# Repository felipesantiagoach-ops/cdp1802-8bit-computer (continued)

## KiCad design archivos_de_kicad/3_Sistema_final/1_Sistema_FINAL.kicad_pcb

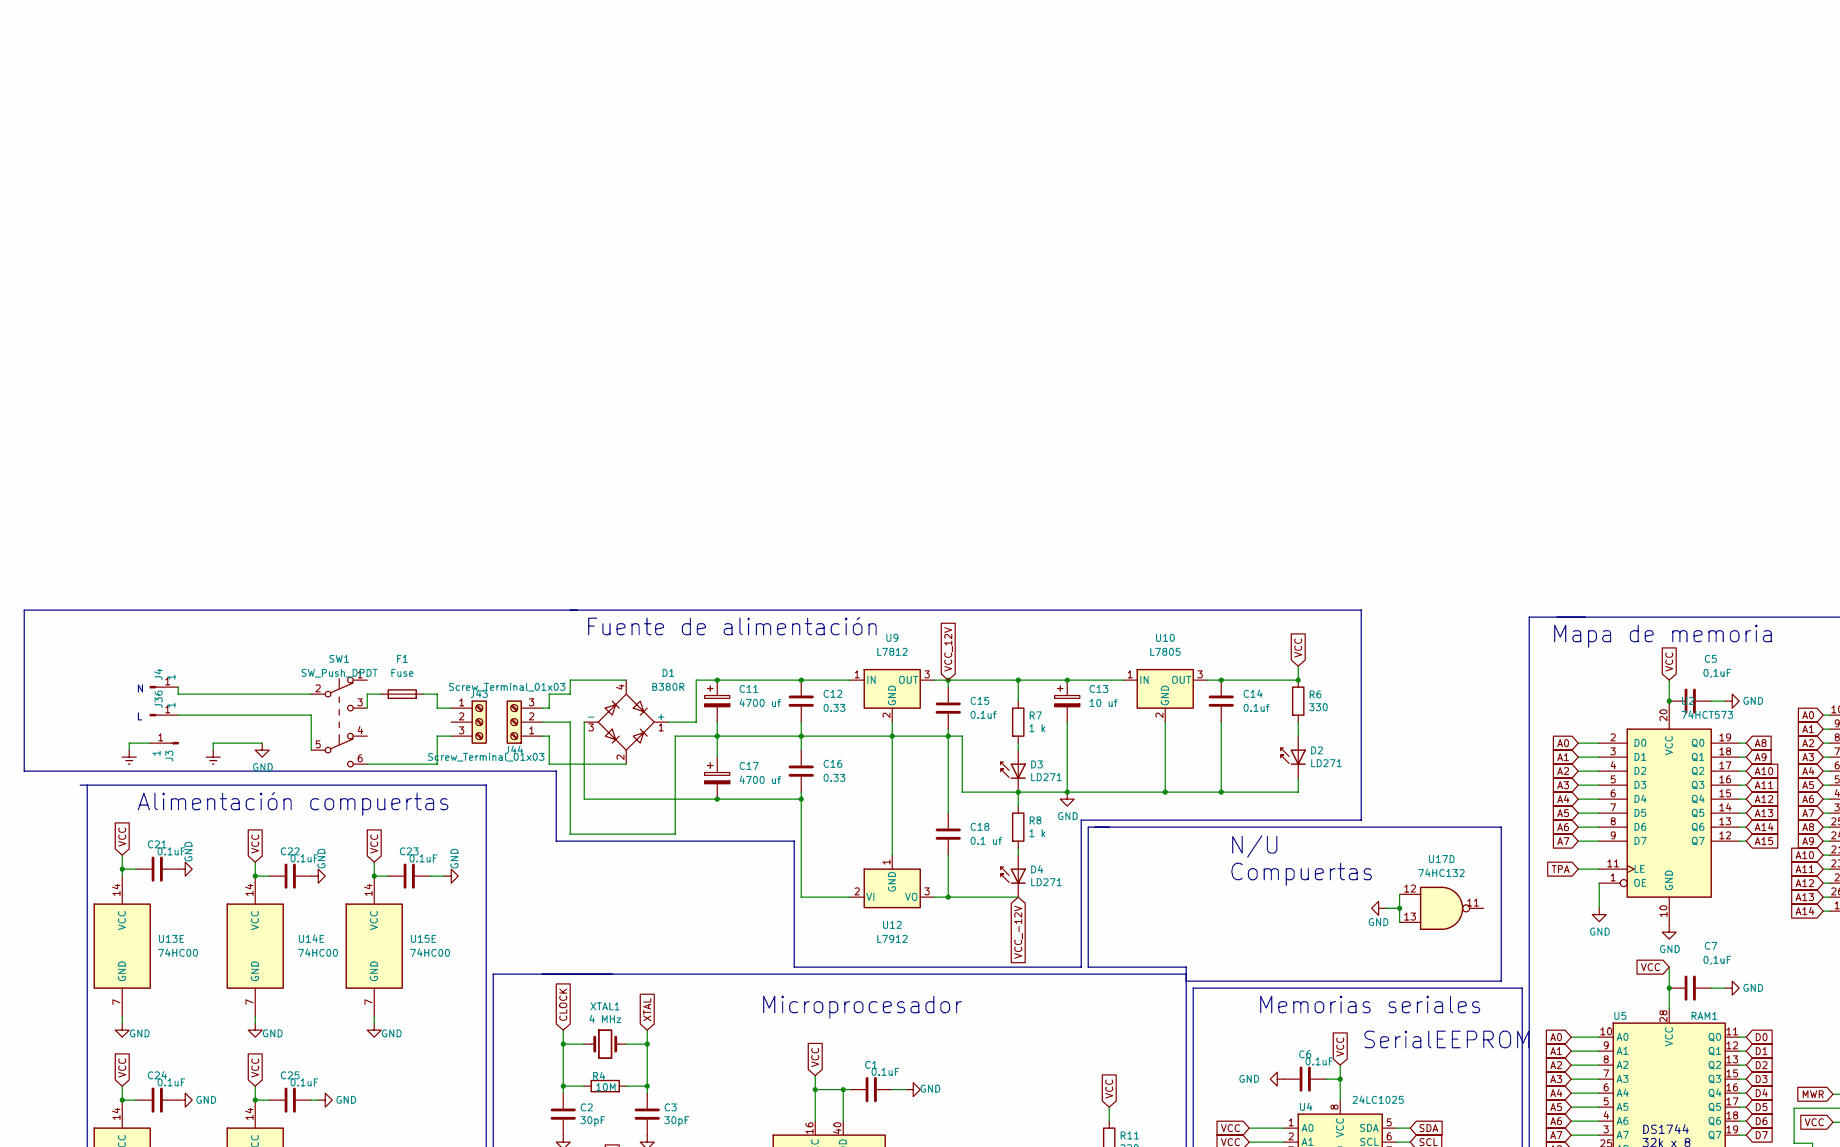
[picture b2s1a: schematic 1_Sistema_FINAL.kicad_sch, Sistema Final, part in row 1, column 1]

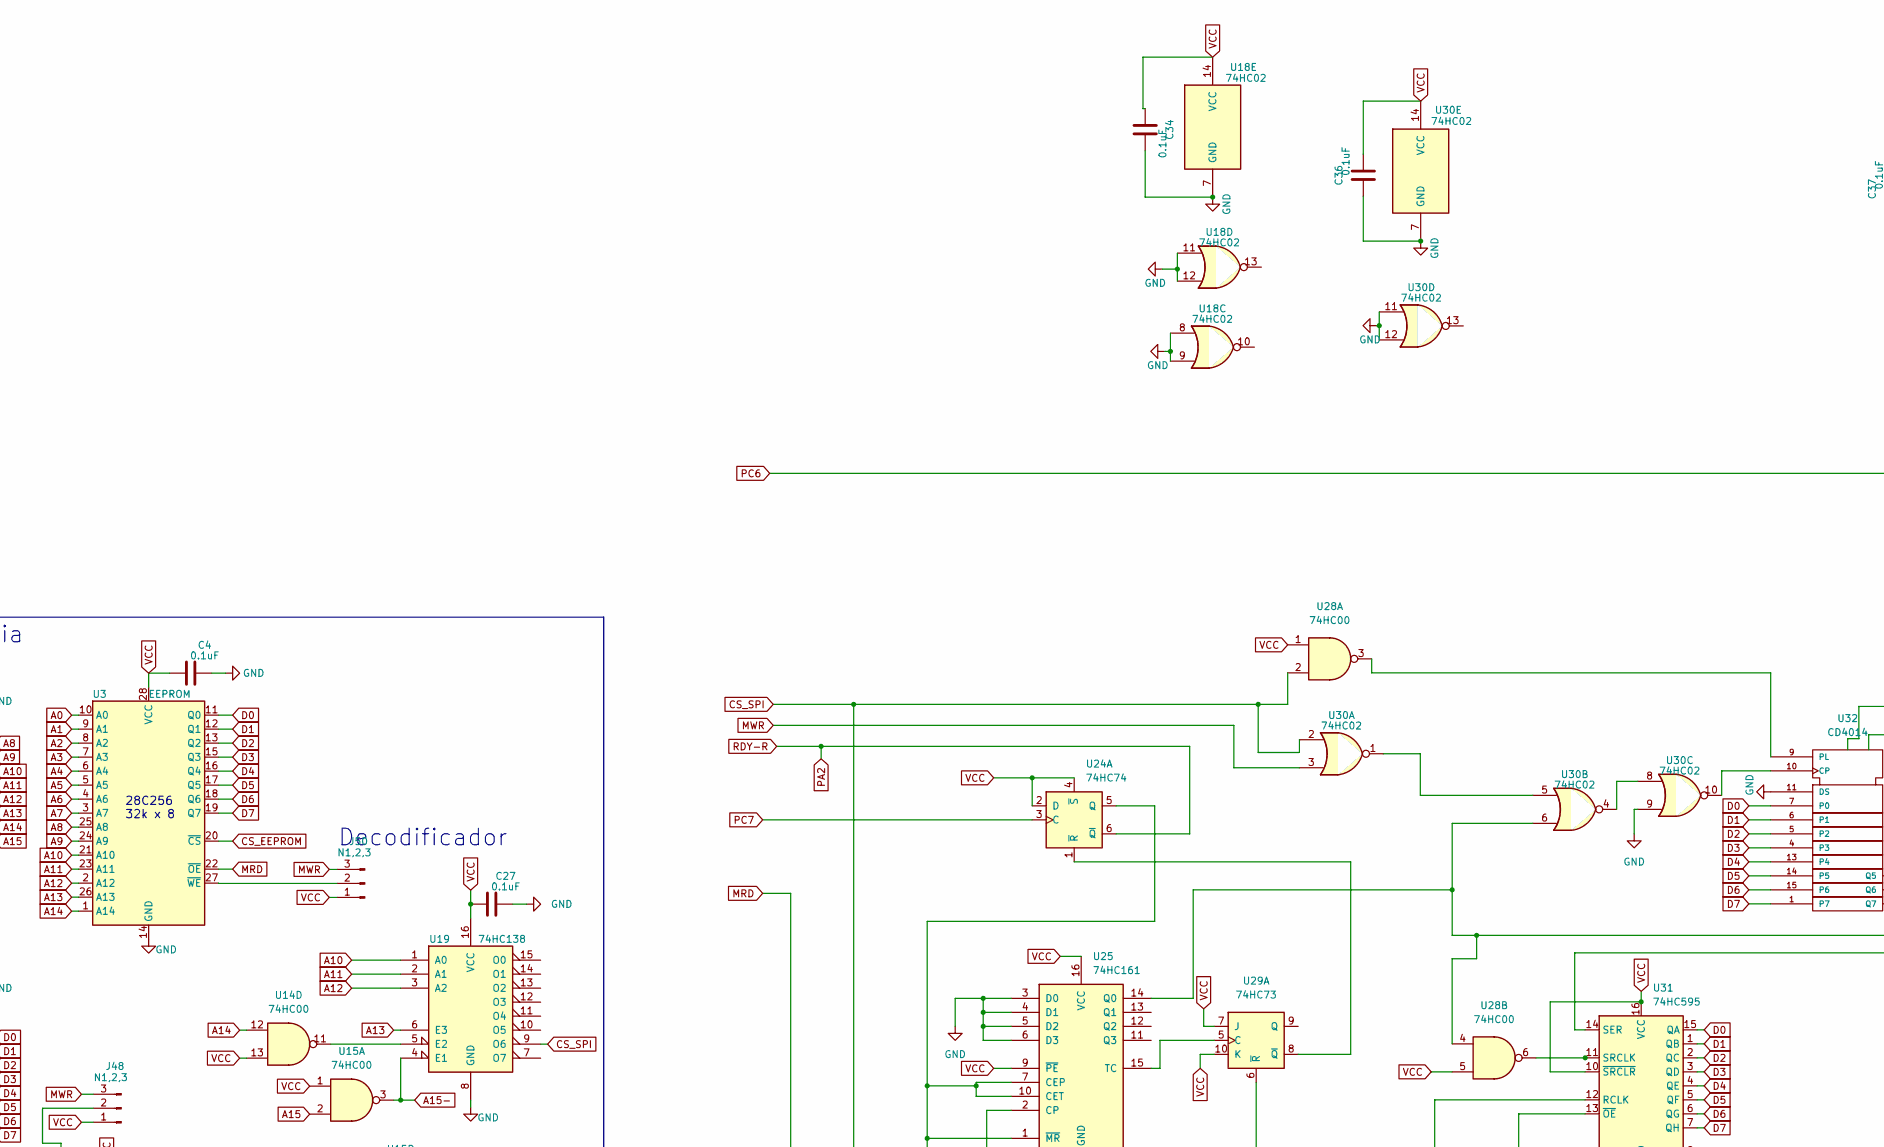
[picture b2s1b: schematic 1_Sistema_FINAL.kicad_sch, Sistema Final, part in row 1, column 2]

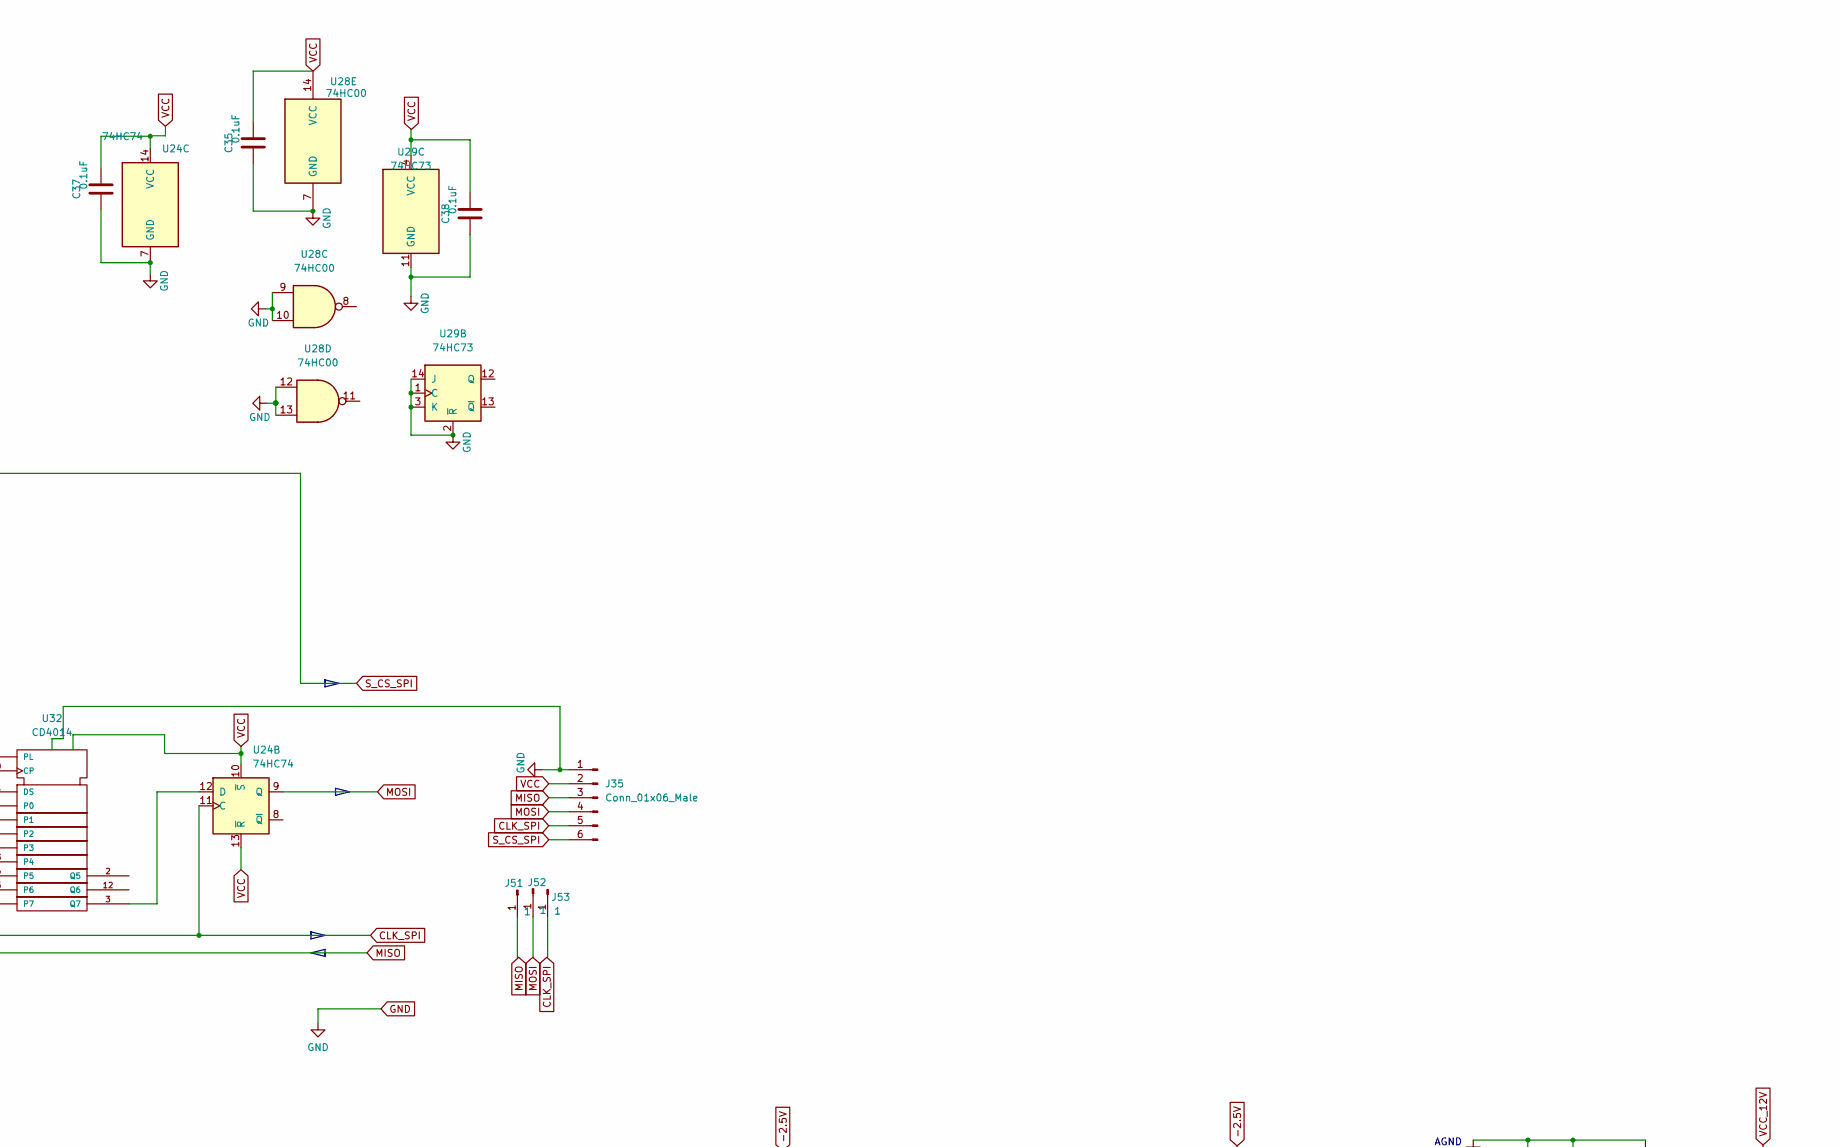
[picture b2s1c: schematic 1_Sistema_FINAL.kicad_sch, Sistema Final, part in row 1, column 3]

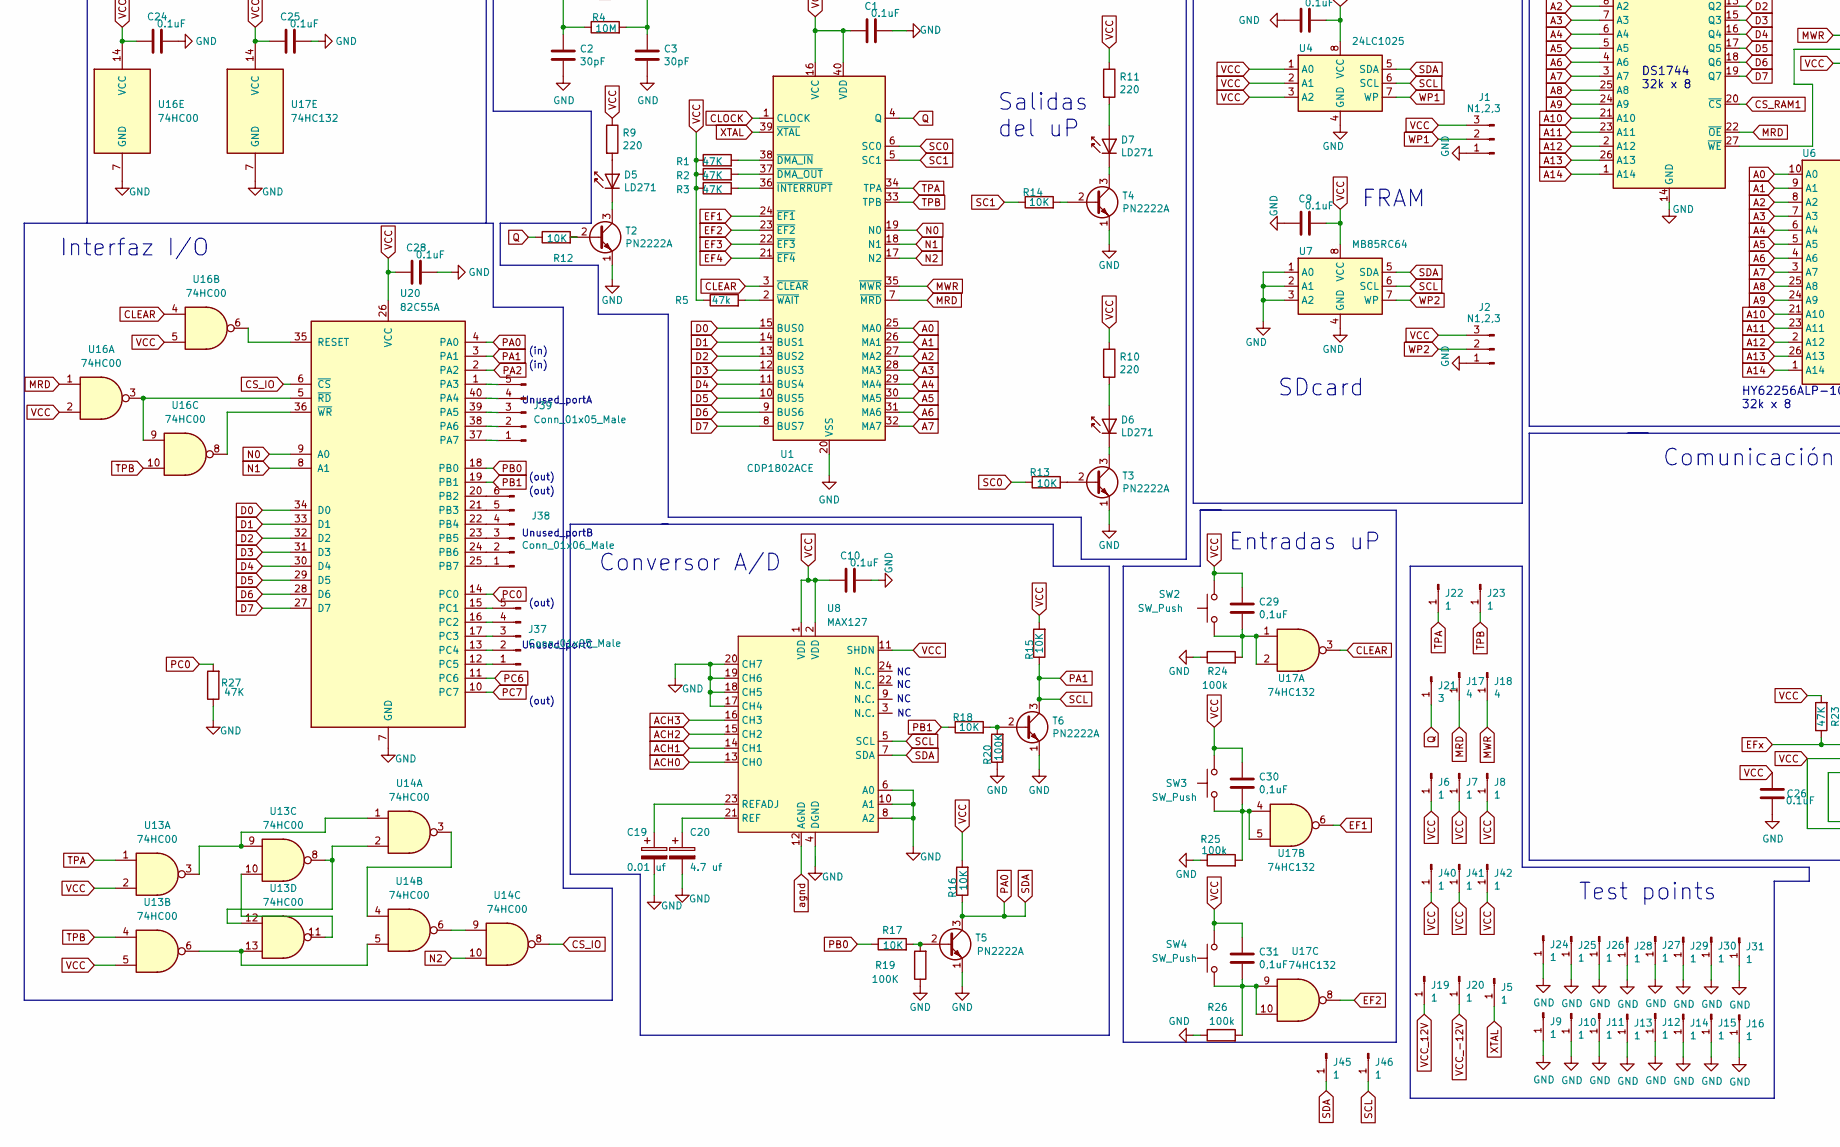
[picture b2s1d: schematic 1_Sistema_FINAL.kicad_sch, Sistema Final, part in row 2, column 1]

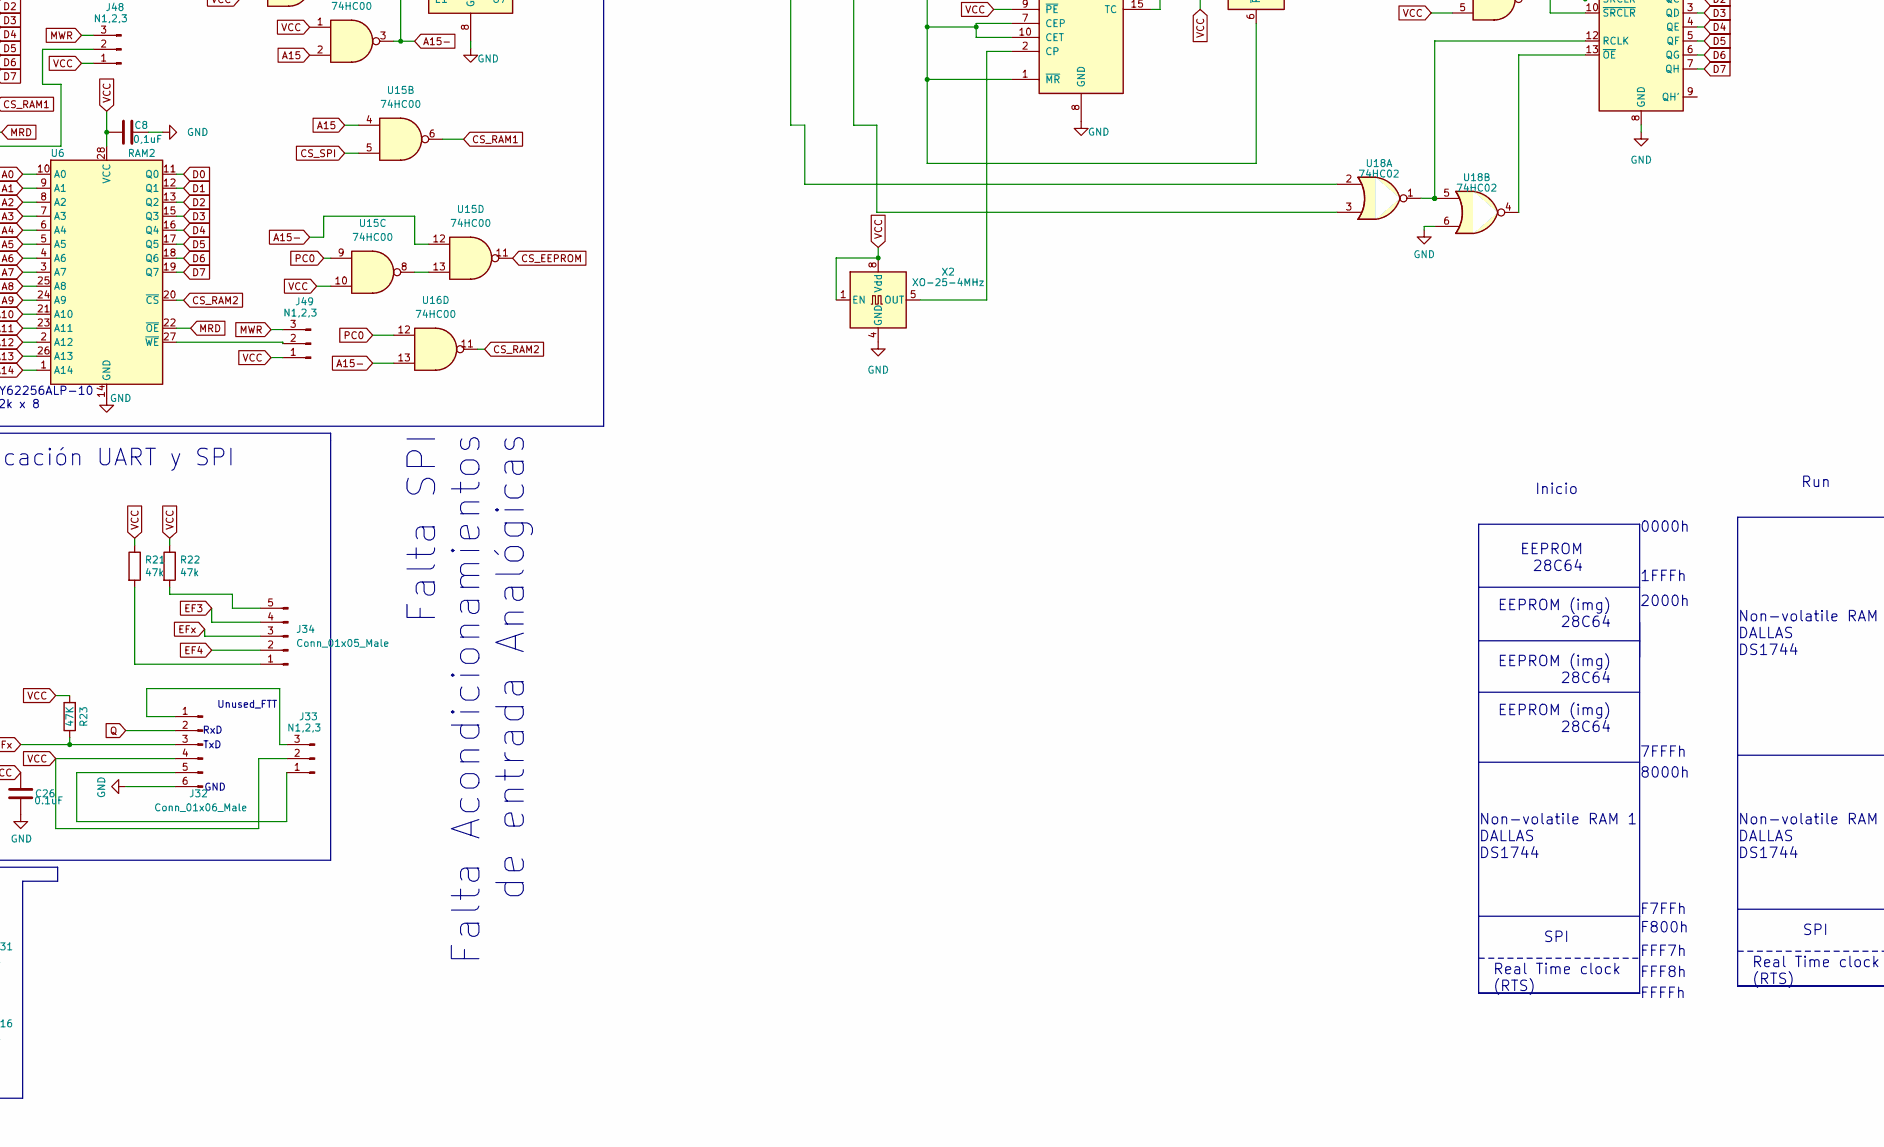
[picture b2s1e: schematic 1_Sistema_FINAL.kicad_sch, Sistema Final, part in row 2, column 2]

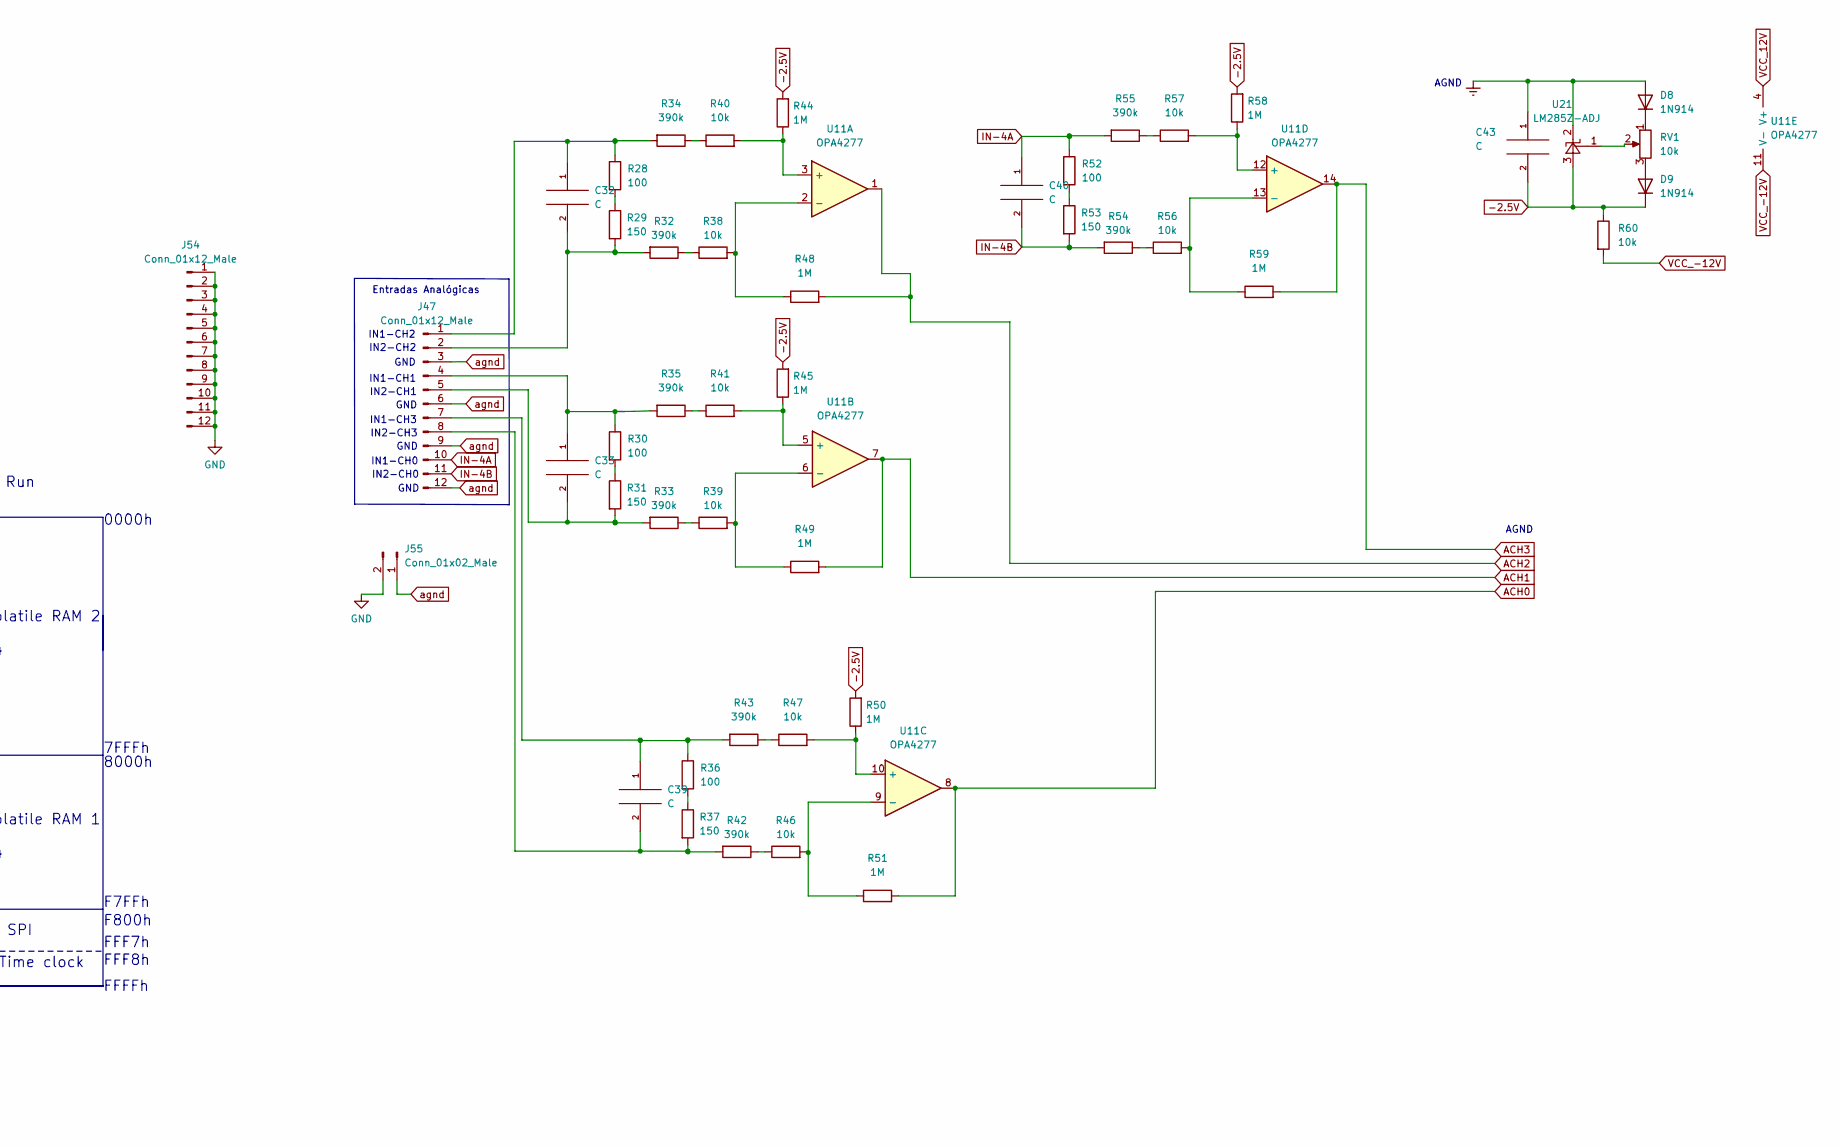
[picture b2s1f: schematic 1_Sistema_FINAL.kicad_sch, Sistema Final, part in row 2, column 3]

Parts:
C1, C4, C6, C9, C10, C21, C22, C23, C24, C25, C26, C27, C28, C34, C35, C36, C37, C38: 0.1uF; C_Disc_D3.0mm_W1.6mm_P2.50mm
C2, C3: 30pF; C_Disc_D4.3mm_W1.9mm_P5.00mm
C5, C7, C8, C29, C30, C31: 0,1uF; C_Disc_D3.0mm_W1.6mm_P2.50mm
C11: 4700 uf; C_Rect_L11.5mm_W4.3mm_P10.00mm_MKT
C12, C16: 0.33; C_Disc_D3.0mm_W1.6mm_P2.50mm
C13: 10 uf; CP_Radial_D5.0mm_P2.00mm
C14, C15: 0.1uf; C_Disc_D3.0mm_W1.6mm_P2.50mm
C17: 4700 uf; C_Rect_L11.5mm_W2.8mm_P10.00mm_MKT
C18: 0.1 uf; C_Disc_D3.0mm_W1.6mm_P2.50mm
C19: 0.01 uf; C_Disc_D3.0mm_W1.6mm_P2.50mm
C20: 4.7 uf; CP_Radial_D5.0mm_P2.00mm
C32, C33, C39, C40, C43: C; C_Disc_D3.0mm_W1.6mm_P2.50mm
D1: B380R; Diode_Bridge_Round_D9.0mm
D2, D3, D4, D5, D6, D7: LD271; LED_D5.0mm
D8, D9: 1N914; D_DO-35_SOD27_P7.62mm_Horizontal
F1: Fuse; fusible_10mm
J1, J2, J33, J48, J49, J50: N1,2,3; PinHeader_1x03_P2.54mm_Vertical
J3, J4, J5, J6, J7, J8, J9, J10, J11, J12, J13, J14, J15, J16, J19, J20, J22, J23, J24, J25, J26, J27, J28, J29, J30, J31, J36, J40, J41, J42, J45, J46, J51, J52, J53: 1; Pin_D1.0mm_L10.0mm
J17, J18: 4; Pin_D1.0mm_L10.0mm
J21: 3; Pin_D1.0mm_L10.0mm
J32, J35, J38: Conn_01x06_Male; PinHeader_1x06_P2.54mm_Vertical
J34, J37, J39: Conn_01x05_Male; PinHeader_1x05_P2.54mm_Vertical
J43, J44: Screw_Terminal_01x03; TerminalBlock_bornier-3_P5.08mm
J47, J54: Conn_01x12_Male; PinHeader_1x12_P2.54mm_Vertical
J55: Conn_01x02_Male; PinHeader_1x02_P2.54mm_Vertical
R1, R2, R3, R23, R27: 47K; R_Axial_DIN0207_L6.3mm_D2.5mm_P10.16mm_Horizontal
R4: 10M; R_Axial_DIN0207_L6.3mm_D2.5mm_P10.16mm_Horizontal
R5: 47k; R_Axial_DIN0207_L6.3mm_D2.5mm_P10.16mm_Horizontal
R6: 330; R_Axial_DIN0207_L6.3mm_D2.5mm_P10.16mm_Horizontal
R7, R8: 1 k; R_Axial_DIN0207_L6.3mm_D2.5mm_P10.16mm_Horizontal
R9, R10, R11: 220; R_Axial_DIN0207_L6.3mm_D2.5mm_P10.16mm_Horizontal
R12, R13, R14, R15, R16, R17, R18: 10K; R_Axial_DIN0207_L6.3mm_D2.5mm_P10.16mm_Horizontal
R19, R20: 100K; R_Axial_DIN0207_L6.3mm_D2.5mm_P10.16mm_Horizontal
R21, R22: 47k; R_Axial_DIN0207_L6.3mm_D2.5mm_P15.24mm_Horizontal
R24, R25, R26: 100k; R_Axial_DIN0207_L6.3mm_D2.5mm_P10.16mm_Horizontal
R28, R30, R36, R52: 100; R_Axial_DIN0207_L6.3mm_D2.5mm_P10.16mm_Horizontal
R29, R31, R37, R53: 150; R_Axial_DIN0207_L6.3mm_D2.5mm_P10.16mm_Horizontal
R32, R33, R34, R35, R42, R43, R54, R55: 390k; R_Axial_DIN0207_L6.3mm_D2.5mm_P10.16mm_Horizontal
R38, R39, R40, R41, R46, R47, R56, R57, R60: 10k; R_Axial_DIN0207_L6.3mm_D2.5mm_P10.16mm_Horizontal
R44, R45, R48, R49, R50, R51, R58, R59: 1M; R_Axial_DIN0207_L6.3mm_D2.5mm_P10.16mm_Horizontal
RV1: 10k; Potentiometer_Bourns_3386C_Horizontal
SW1: SW_Push_DPDT; llave_6pin
SW2, SW3, SW4: SW_Push; SW_PUSH_6mm_H4.3mm
T2, T3, T4, T5, T6: PN2222A; TO-92L_Wide
U1: CDP1802ACE; DIP-40_W15.24mm_LongPads
U2: 74HCT573; DIP-20_W7.62mm_Socket_LongPads
U3: EEPROM; DIP-28_W15.24mm_LongPads
U4: 24LC1025; DIP-8_W7.62mm_LongPads
U5: RAM1; DIP-28_W15.24mm_LongPads
U6: RAM2; DIP-28_W15.24mm_LongPads
U7: MB85RC64; DIP-8_W8.89mm_SMDSocket_LongPads
U8: MAX127; DIP-24_W7.62mm_LongPads
U9: L7812; TO-220-3_Vertical
U10: L7805; TO-220-3_Vertical
U11: OPA4277; DIP-14_W7.62mm_LongPads
U12: L7912; TO-220-3_Vertical
U13, U14, U15, U16, U28: 74HC00; DIP-14_W7.62mm_LongPads
U17: 74HC132; DIP-14_W7.62mm_LongPads
U18, U30: 74HC02; DIP-14_W7.62mm_LongPads
U19: 74HC138; DIP-16_W7.62mm_LongPads
U20: 82C55A; DIP-40_W15.24mm
U21: LM285Z-ADJ; TO-92S_Wide
U24: 74HC74; DIP-14_W7.62mm_LongPads
U25: 74HC161; DIP-16_W7.62mm_LongPads
U29: 74HC73; DIP-14_W7.62mm_LongPads
U31: 74HC595; DIP-16_W7.62mm_LongPads
U32: CD4014; DIP-16_W7.62mm_LongPads
X2: XO-25-4MHz; Oscillator_SeikoEpson_SG-8002DC
XTAL1: 4 MHz; Crystal_HC18-U_Vertical

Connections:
-2.5V: C43.2, D9.1 (K), R44.2, R45.2, R50.2, R58.2, R60.1, U21.3 (A)
A0: U1.25 (MA0), U2.2 (D0), U3.10 (A0), U5.10 (A0), U6.10 (A0)
A1: U1.26 (MA1), U2.3 (D1), U3.9 (A1), U5.9 (A1), U6.9 (A1)
A2: U1.27 (MA2), U2.4 (D2), U3.8 (A2), U5.8 (A2), U6.8 (A2)
A3: U1.28 (MA3), U2.5 (D3), U3.7 (A3), U5.7 (A3), U6.7 (A3)
A4: U1.29 (MA4), U2.6 (D4), U3.6 (A4), U5.6 (A4), U6.6 (A4)
A5: U1.30 (MA5), U2.7 (D5), U3.5 (A5), U5.5 (A5), U6.5 (A5)
A6: U1.31 (MA6), U2.8 (D6), U3.4 (A6), U5.4 (A6), U6.4 (A6)
A7: U1.32 (MA7), U2.9 (D7), U3.3 (A7), U5.3 (A7), U6.3 (A7)
A8: U2.19 (Q0), U3.25 (A8), U5.25 (A8), U6.25 (A8)
A9: U2.18 (Q1), U3.24 (A9), U5.24 (A9), U6.24 (A9)
A10: U2.17 (Q2), U3.21 (A10), U5.21 (A10), U6.21 (A10), U19.1 (A0)
A11: U2.16 (Q3), U3.23 (A11), U5.23 (A11), U6.23 (A11), U19.2 (A1)
A12: U2.15 (Q4), U3.2 (A12), U5.2 (A12), U6.2 (A12), U19.3 (A2)
A13: U2.14 (Q5), U3.26 (A13), U5.26 (A13), U6.26 (A13), U19.6 (E3)
A14: U2.13 (Q6), U3.1 (A14), U5.1 (A14), U6.1 (A14), U14.12
A15: U2.12 (Q7), U15.2, U15.4
A15-: U15.3, U15.12, U16.13, U19.4 (E1)
ACH0: R51.2, U8.13 (CH0), U11.8
ACH1: R49.2, U8.14 (CH1), U11.7
ACH2: R48.2, U8.15 (CH2), U11.1
ACH3: R59.2, U8.16 (CH3), U11.14
CLEAR: U1.3 (~CLEAR), U16.4, U17.3
CLK_SPI: J35.5, J53.1, U24.11 (C), U25.14 (Q0), U28.4, U30.6
CLOCK: C2.1, R4.1, U1.1 (CLOCK), XTAL1.1
CS_EEPROM: U3.20 (~CS), U15.11
CS_IO: U14.8, U20.6 (~CS)
CS_RAM1: U5.20 (~CS), U15.6
CS_RAM2: U6.20 (~CS), U16.11
CS_SPI: U15.5, U18.3, U19.9 (O6), U28.2, U30.2
D0: U1.15 (BUS0), U3.11 (Q0), U5.11 (Q0), U6.11 (Q0), U20.34 (D0), U31.15 (QA), U32.7 (P0)
D1: U1.14 (BUS1), U3.12 (Q1), U5.12 (Q1), U6.12 (Q1), U20.33 (D1), U31.1 (QB), U32.6 (P1)
D2: U1.13 (BUS2), U3.13 (Q2), U5.13 (Q2), U6.13 (Q2), U20.32 (D2), U31.2 (QC), U32.5 (P2)
D3: U1.12 (BUS3), U3.15 (Q3), U5.15 (Q3), U6.15 (Q3), U20.31 (D3), U31.3 (QD), U32.4 (P3)
D4: U1.11 (BUS4), U3.16 (Q4), U5.16 (Q4), U6.16 (Q4), U20.30 (D4), U31.4 (QE), U32.13 (P4)
D5: U1.10 (BUS5), U3.17 (Q5), U5.17 (Q5), U6.17 (Q5), U20.29 (D5), U31.5 (QF), U32.14 (P5)
D6: U1.9 (BUS6), U3.18 (Q6), U5.18 (Q6), U6.18 (Q6), U20.28 (D6), U31.6 (QG), U32.15 (P6)
D7: U1.8 (BUS7), U3.19 (Q7), U5.19 (Q7), U6.19 (Q7), U20.27 (D7), U31.7 (QH), U32.1 (P7)
EF1: U1.24 (~EF1), U17.6
EF2: U1.23 (~EF2), U17.8
EF3: J34.4, U1.22 (~EF3)
EF4: J34.2, U1.21 (~EF4)
EFx: J32.3, J34.3, R23.1
GND: C1.2, C2.2, C3.2, C4.2, C5.2, C6.1, C7.2, C8.2, C9.1, C10.2, C11.2, C12.2, C13.2, C14.2, C15.2, C16.1, C17.1, C18.1, C19.2, C20.2, C21.2, C22.2, C23.2, C24.2, C25.2, C26.2, C27.2, C28.2, C34.2, C35.1, C36.1, C37.1, C38.1, C43.1, D2.1 (K), D3.1 (K), D8.2 (A), J1.1, J2.1, J3.1, J9.1, J10.1, J11.1, J12.1, J13.1, J14.1, J15.1, J16.1, J24.1, J25.1, J26.1, J27.1, J28.1, J29.1, J30.1, J31.1, J32.6, J35.1, J44.2, J54.1, J54.2, J54.3, J54.4, J54.5, J54.6, J54.7, J54.8, J54.9, J54.10, J54.11, J54.12, J55.2, R8.1, R19.1, R20.1, R24.1, R25.1, R26.1, R27.1, T2.1 (E), T3.1 (E), T4.1 (E), T5.1 (E), T6.1 (E), U1.20 (VSS), U2.1 (OE), U2.10 (GND), U3.14 (GND), U4.4 (GND), U5.14 (GND), U6.14 (GND), U7.1 (A0), U7.2 (A1), U7.3 (A2), U7.4 (GND), U8.4 (DGND), U8.6 (A0), U8.8 (A2), U8.10 (A1), U8.17 (CH4), U8.18 (CH5), U8.19 (CH6), U8.20 (CH7), U9.2 (GND), U10.2 (GND), U12.1 (GND), U13.7 (GND), U14.7 (GND), U15.7 (GND), U16.7 (GND), U17.7 (GND), U17.12, U17.13, U18.6, U18.7 (GND), U18.8, U18.9, U18.11, U18.12, U19.8 (GND), U20.7 (GND), U21.2 (K), U24.7 (GND), U25.3 (D0), U25.4 (D1), U25.5 (D2), U25.6 (D3), U25.8 (GND), U28.7 (GND), U28.9, U28.10, U28.12, U28.13, U29.1 (C), U29.2 (~R), U29.3 (K), U29.11 (GND), U29.14 (J), U30.7 (GND), U30.9, U30.11, U30.12, U31.8 (GND), U32.8 (Vss), U32.11 (DS), X2.4 (GND)
IN-4A: C40.1, J47.10, R52.1, R55.2
IN-4B: C40.2, J47.11, R53.2, R54.2
MISO: J35.3, J51.1, U31.14 (SER)
MOSI: J35.4, J52.1, U24.9 (Q)
MRD: J17.1, U1.7 (~MRD), U3.22 (~OE), U5.22 (~OE), U6.22 (~OE), U16.1, U18.2
MWR: J18.1, J48.3, J49.3, J50.3, U1.35 (~MWR), U30.3
N0: U1.19 (N0), U20.9 (A0)
N1: U1.18 (N1), U20.8 (A1)
N2: U1.17 (N2), U14.10
unnamed: C11.1, C12.1, D1.1 (+), U9.1 (IN)
unnamed: C16.2, C17.2, D1.3 (-), U12.2 (VI)
unnamed: C19.1, U8.23 (REFADJ)
unnamed: C20.1, U8.21 (REF)
unnamed: C29.2, R24.2, SW2.1, U17.1, U17.2
unnamed: C30.2, R25.2, SW3.1, U17.4, U17.5
unnamed: C31.2, R26.2, SW4.1, U17.9, U17.10
unnamed: C32.1, J47.1, R28.1, R34.2
unnamed: C32.2, J47.2, R29.2, R32.2
unnamed: C33.1, J47.4, R30.1, R35.2
unnamed: C33.2, J47.5, R31.2, R33.2
unnamed: C39.1, J47.7, R36.1, R43.2
unnamed: C39.2, J47.8, R37.2, R42.2
unnamed: D1.2, J44.1
unnamed: D1.4, J44.3
unnamed: D2.2 (A), R6.2
unnamed: D3.2 (A), R7.2
unnamed: D4.2 (A), R8.2
unnamed: D5.1 (K), T2.3 (C)
unnamed: D5.2 (A), R9.2
unnamed: D6.1 (K), T3.3 (C)
unnamed: D6.2 (A), R10.2
unnamed: D7.1 (K), T4.3 (C)
unnamed: D7.2 (A), R11.2
unnamed: D8.1 (K), RV1.1
unnamed: D9.2 (A), RV1.3
unnamed: F1.1, SW1.3 (C)
unnamed: F1.2, J43.1
unnamed: J4.1, SW1.2 (B)
unnamed: J32.1, J33.3
unnamed: J32.5, J33.1
unnamed: J34.1, R21.2
unnamed: J34.5, R22.2
unnamed: J36.1, SW1.5 (B)
unnamed: J37.1, U20.12 (PC5)
unnamed: J37.2, U20.13 (PC4)
unnamed: J37.3, U20.17 (PC3)
unnamed: J37.4, U20.16 (PC2)
unnamed: J37.5, U20.15 (PC1)
unnamed: J38.1, U20.25 (PB7)
unnamed: J38.2, U20.24 (PB6)
unnamed: J38.3, U20.23 (PB5)
unnamed: J38.4, U20.22 (PB4)
unnamed: J38.5, U20.21 (PB3)
unnamed: J38.6, U20.20 (PB2)
unnamed: J39.1, U20.37 (PA7)
unnamed: J39.2, U20.38 (PA6)
unnamed: J39.3, U20.39 (PA5)
unnamed: J39.4, U20.40 (PA4)
unnamed: J39.5, U20.1 (PA3)
unnamed: J43.3, SW1.6 (C)
unnamed: J48.2, U5.27 (~WE)
unnamed: J49.2, U6.27 (~WE)
unnamed: J50.2, U3.27 (~WE)
unnamed: R1.2, U1.38 (~DMA_IN)
unnamed: R2.2, U1.37 (~DMA_OUT)
unnamed: R3.2, U1.36 (~INTERRUPT)
unnamed: R5.2, U1.2 (~WAIT)
unnamed: R12.2, T2.2 (B)
unnamed: R13.2, T3.2 (B)
unnamed: R14.2, T4.2 (B)
unnamed: R17.2, R19.2, T5.2 (B)
unnamed: R18.2, R20.2, T6.2 (B)
unnamed: R28.2, R29.1
unnamed: R30.2, R31.1
unnamed: R32.1, R38.1
unnamed: R33.1, R39.1
unnamed: R34.1, R40.1
unnamed: R35.1, R41.1
unnamed: R36.2, R37.1
unnamed: R38.2, R48.1, U11.2 (-)
unnamed: R39.2, R49.1, U11.6 (-)
unnamed: R40.2, R44.1, U11.3 (+)
unnamed: R41.2, R45.1, U11.5 (+)
unnamed: R42.1, R46.1
unnamed: R43.1, R47.1
unnamed: R46.2, R51.1, U11.9 (-)
unnamed: R47.2, R50.1, U11.10 (+)
unnamed: R52.2, R53.1
unnamed: R54.1, R56.1
unnamed: R55.1, R57.1
unnamed: R56.2, R59.1, U11.13 (-)
unnamed: R57.2, R58.1, U11.12 (+)
unnamed: RV1.2, U21.1 (FB)
unnamed: U13.3, U13.9, U14.1
unnamed: U13.10, U13.11
unnamed: U13.8, U13.12, U14.2
unnamed: U13.6, U13.13, U14.5
unnamed: U14.3, U14.4
unnamed: U14.6, U14.9
unnamed: U14.11, U19.5 (E2)
unnamed: U15.8, U15.13
unnamed: U16.3, U16.9, U20.5 (~RD)
unnamed: U16.6, U20.35 (RESET)
unnamed: U16.8, U20.36 (~WR)
unnamed: U18.1, U18.5, U31.12 (RCLK)
unnamed: U18.4, U31.13 (~OE)
unnamed: U24.1 (~R), U29.8 (~Q)
unnamed: U24.5 (Q), U25.1 (~MR), U25.7 (CEP), U25.10 (CET), U29.6 (~R)
unnamed: U24.12 (D), U32.3 (Q7)
unnamed: U25.2 (CP), X2.5 (OUT)
unnamed: U28.3, U32.9 (PL)
unnamed: U28.6, U31.11 (SRCLK)
unnamed: U30.1, U30.5
unnamed: U30.4, U30.8
unnamed: U30.10, U32.10 (CP)
PA0: J45.1, R16.1, T5.3 (C), U4.5 (SDA), U7.5 (SDA), U8.7 (SDA), U20.4 (PA0)
PA1: J46.1, R15.1, T6.3 (C), U4.6 (SCL), U7.6 (SCL), U8.5 (SCL), U20.3 (PA1)
PA2: U20.2 (PA2), U24.6 (~Q)
PB0: R17.1, U20.18 (PB0)
PB1: R18.1, U20.19 (PB1)
PC0: R27.2, U15.9, U16.12, U20.14 (PC0)
PC6: J35.6, U20.11 (PC6)
PC7: U20.10 (PC7), U24.3 (C)
Q: J21.1, J32.2, R12.1, U1.4 (Q)
SC0: R13.1, U1.6 (SC0)
SC1: R14.1, U1.5 (SC1)
TPA: J22.1, U1.34 (TPA), U2.11 (LE), U13.1
TPB: J23.1, U1.33 (TPB), U13.4, U16.10
VCC: C1.1, C4.1, C5.1, C6.2, C7.1, C8.1, C9.2, C10.1, C14.1, C21.1, C22.1, C23.1, C24.1, C25.1, C26.1, C27.1, C28.1, C29.1, C30.1, C31.1, C34.1, C35.2, C36.2, C37.2, C38.2, J1.3, J2.3, J6.1, J7.1, J8.1, J32.4, J33.2, J35.2, J40.1, J41.1, J42.1, J48.1, J49.1, J50.1, R1.1, R2.1, R3.1, R5.1, R6.1, R9.1, R10.1, R11.1, R15.2, R16.2, R21.1, R22.1, R23.2, SW2.2, SW3.2, SW4.2, U1.16 (VCC), U1.40 (VDD), U2.20 (VCC), U3.28 (VCC), U4.1 (A0), U4.2 (A1), U4.3 (A2), U4.8 (VCC), U5.28 (VCC), U6.28 (VCC), U7.8 (VCC), U8.1 (VDD), U8.2 (VDD), U8.11 (SHDN), U10.3 (OUT), U13.2, U13.5, U13.14 (VCC), U14.13, U14.14 (VCC), U15.1, U15.10, U15.14 (VCC), U16.2, U16.5, U16.14 (VCC), U17.14 (VCC), U18.14 (VCC), U19.16 (VCC), U20.26 (VCC), U24.2 (D), U24.4 (~S), U24.10 (~S), U24.13 (~R), U24.14 (VCC), U25.9 (~PE), U25.16 (VCC), U28.1, U28.5, U28.14 (VCC), U29.4 (VCC), U29.7 (J), U29.10 (K), U30.14 (VCC), U31.10 (~SRCLR), U31.16 (VCC), U32.16 (Vdd), X2.1 (EN), X2.8 (Vdd)
VCC_12V: C13.1, C15.1, J19.1, R7.1, U9.3 (OUT), U10.1 (IN), U11.4 (V+)
VCC_-12V: C18.2, D4.1 (K), J20.1, R60.2, U11.11 (V-), U12.3 (VO)
WP1: J1.2, U4.7 (WP)
WP2: J2.2, U7.7 (WP)
XTAL: C3.1, J5.1, R4.2, U1.39 (~XTAL), XTAL1.2
agnd: J47.3, J47.6, J47.9, J47.12, J55.1, U8.12 (AGND)

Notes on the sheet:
Non-volatile RAM 2 DALLAS DS1744
FRAM
FFFFh
Comunicación UART y SPI
Decodificador
Unused_portA
EEPROM 28C64
Microprocesador
F800h
0000h
Mapa de memoria
Unused_portB
GND
Falta SPI Falta Acondicionamientos de entrada Analógicas
IN1-CH3
Interfaz I/O
Test points
Run
Non-volatile RAM 1 DALLAS DS1744
Alimentación compuertas
AGND
1FFFh
IN2-CH0
IN2-CH2
FFF7h
Unused_FTT
7FFFh
(out)
F7FFh
TxD
Entradas Analógicas
Entradas uP
DS1744 32k x 8
SerialEEPROM
SPI
(in)
Memorias seriales
RxD
28C256 32k x 8
Real Time clock (RTS)

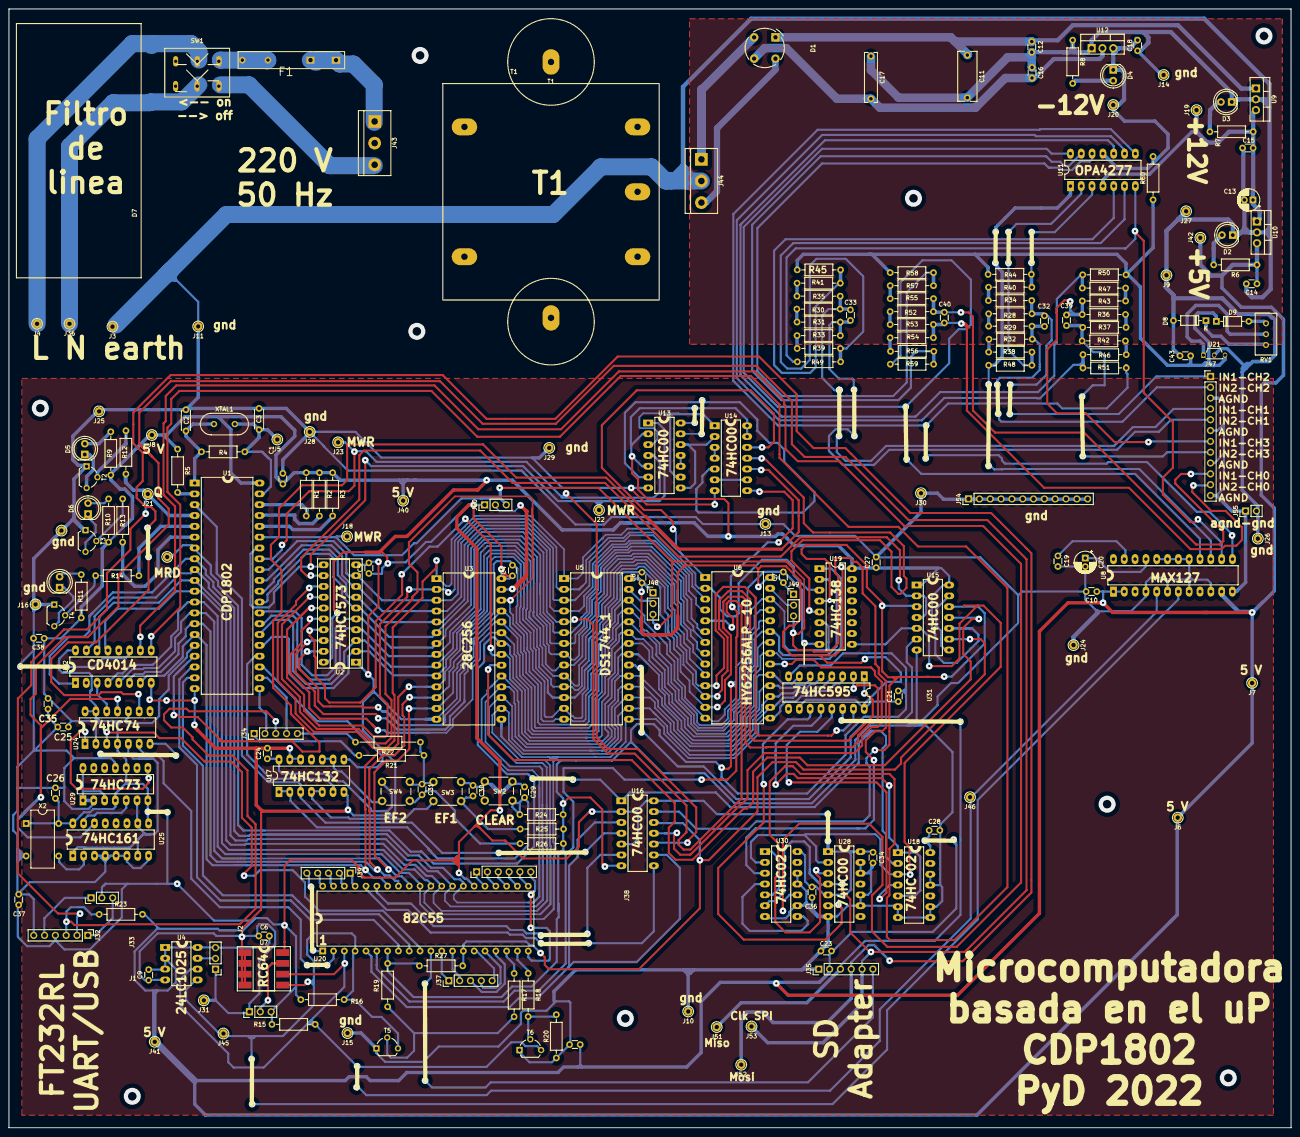
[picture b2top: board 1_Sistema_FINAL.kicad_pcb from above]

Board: 2 copper layers, 301.0 x 262.6 mm, 207 parts (0 on the bottom side), 179 nets.

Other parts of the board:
T1: Transformer_1P_SS; trafo_puntomedio
